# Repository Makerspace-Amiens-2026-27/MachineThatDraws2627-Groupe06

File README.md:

# Dessinator 2000

> [!IMPORTANT]
> **À modifier** : Le nom est arbitraire et voué à etre changé.
> Je l'ai mis temporairement pour des tests (Sacha S).

Une phrase qui explique ce que fait le projet et pour qui.

- **Documentation :** [site du projet](https://makerspace-amiens-2026-27.github.io/MachineThatDraws2627-Groupe06/) (sources dans [`docs/`](docs/))
- **Fichiers du projet :** [`project/`](project/) (CAO, électronique, code)

## Équipe

| Membre | Formation | Compte GitHub |
|---|---|---|
| Sacha SZESTAK | joueur pokemon go  | [@Sacha-SZESTAK](https://github.com/sacha-SZESTAK) |
| Sacha HALEZA | tryharder GD | [@Sacha-HALEZA](https://github.com/sachahaleza-stack) |
| Adrien SERVANT | consommateur aguerri du distributeur | [@Adrien-SERVANT](https://github.com/Adrien-Servant) |
| Samuel MOATTI | Consommateur engagé au distributeur | [@Samuel-MOATTI](https://github.com/SamuelMOATTI) |
| Louis DUBRAY | PNJ  | [@Louis-DUBAY](https://github.com/louis-DB) |

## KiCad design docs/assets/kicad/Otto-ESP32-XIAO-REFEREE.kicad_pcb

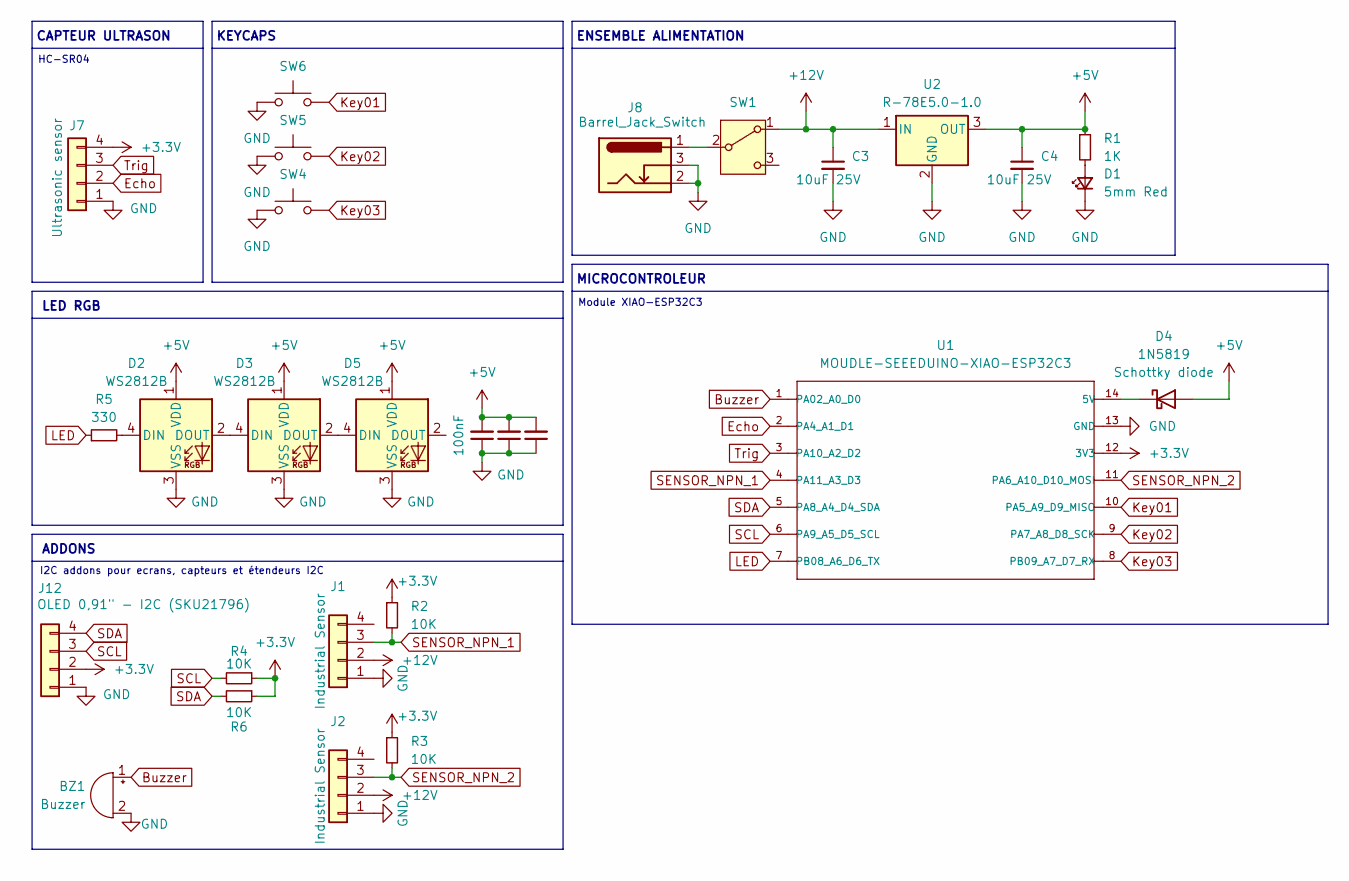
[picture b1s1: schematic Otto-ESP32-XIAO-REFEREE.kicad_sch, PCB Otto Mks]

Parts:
BZ1: Buzzer; Buzzer_12x9.5RM7.6
C3, C4: 10uF 25V; C_Disc_D6.0mm_W2.5mm_P5.00mm
C5, C6, C7: 100nF; C_1206_3216Metric_Pad1.33x1.80mm_HandSolder
D1: 5mm Red; LED_1206_3216Metric_Pad1.42x1.75mm_HandSolder
D2, D3, D5: WS2812B; LED_WS2812B_PLCC4_5.0x5.0mm_P3.2mm
D4: 1N5819; D_A-405_P7.62mm_Horizontal
J1, J2: Industrial Sensor; Molex_KK-254_AE-6410-04A_1x04_P2.54mm_Vertical
J7: Ultrasonic sensor; PinSocket_1x04_P2.54mm_Vertical
J8: Barrel_Jack_Switch; BarrelJack_Horizontal
J12: OLED 0,91" - I2C (SKU21796); PinSocket_1x04_P2.54mm_Vertical
R1: 1K; R_1206_3216Metric_Pad1.30x1.75mm_HandSolder
R2, R3, R4, R6: 10K; R_1206_3216Metric_Pad1.30x1.75mm_HandSolder
R5: 330; R_1206_3216Metric_Pad1.30x1.75mm_HandSolder
SW1: SW_SPDT; SW_100SP1T1B4M2QE
SW4, SW5, SW6: CherryMX; SW_Cherry_MX_1.00u_PCB
U1: MOUDLE-SEEEDUINO-XIAO-ESP32C3; XIAO-ESP32C3-DIP
U2: R-78E5.0-1.0; Converter_DCDC_RECOM_R-78E-0.5_THT

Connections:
+3.3V: J7.4, J12.2, R2.1, R3.1, R4.1, R6.1, U1.12 (3V3)
+5V: C4.1, C5.2, C6.2, C7.2, D2.1 (VDD), D3.1 (VDD), D4.2 (A), D5.1 (VDD), R1.1, U2.3 (OUT)
+12V: C3.1, J1.2, J2.2, SW1.1 (A), U2.1 (IN)
Buzzer: BZ1.1 (+), U1.1 (PA02_A0_D0)
Echo: J7.2, U1.2 (PA4_A1_D1)
GND: BZ1.2 (-), C3.2, C4.2, C5.1, C6.1, C7.1, D1.1 (K), D2.3 (VSS), D3.3 (VSS), D5.3 (VSS), J1.1, J2.1, J7.1, J8.2, J8.3, J12.1, SW4.1, SW5.1, SW6.1, U1.13 (GND), U2.2 (GND)
Key01: SW6.2, U1.10 (PA5_A9_D9_MISO)
Key02: SW5.2, U1.9 (PA7_A8_D8_SCK)
Key03: SW4.2, U1.8 (PB09_A7_D7_RX)
LED: R5.1, U1.7 (PB08_A6_D6_TX)
unnamed: D1.2 (A), R1.2
unnamed: D2.4 (DIN), R5.2
unnamed: D2.2 (DOUT), D3.4 (DIN)
unnamed: D3.2 (DOUT), D5.4 (DIN)
unnamed: D4.1 (K), U1.14 (5V)
unnamed: J8.1, SW1.2 (B)
SCL: J12.3, R4.2, U1.6 (PA9_A5_D5_SCL)
SDA: J12.4, R6.2, U1.5 (PA8_A4_D4_SDA)
SENSOR_NPN_1: J1.3, R2.2, U1.4 (PA11_A3_D3)
SENSOR_NPN_2: J2.3, R3.2, U1.11 (PA6_A10_D10_MOSI)
Trig: J7.3, U1.3 (PA10_A2_D2)

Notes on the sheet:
HC-SR04
CAPTEUR ULTRASON
LED RGB
ADDONS
ENSEMBLE ALIMENTATION
KEYCAPS
Module XIAO-ESP32C3
I2C addons pour ecrans, capteurs et étendeurs I2C
MICROCONTROLEUR

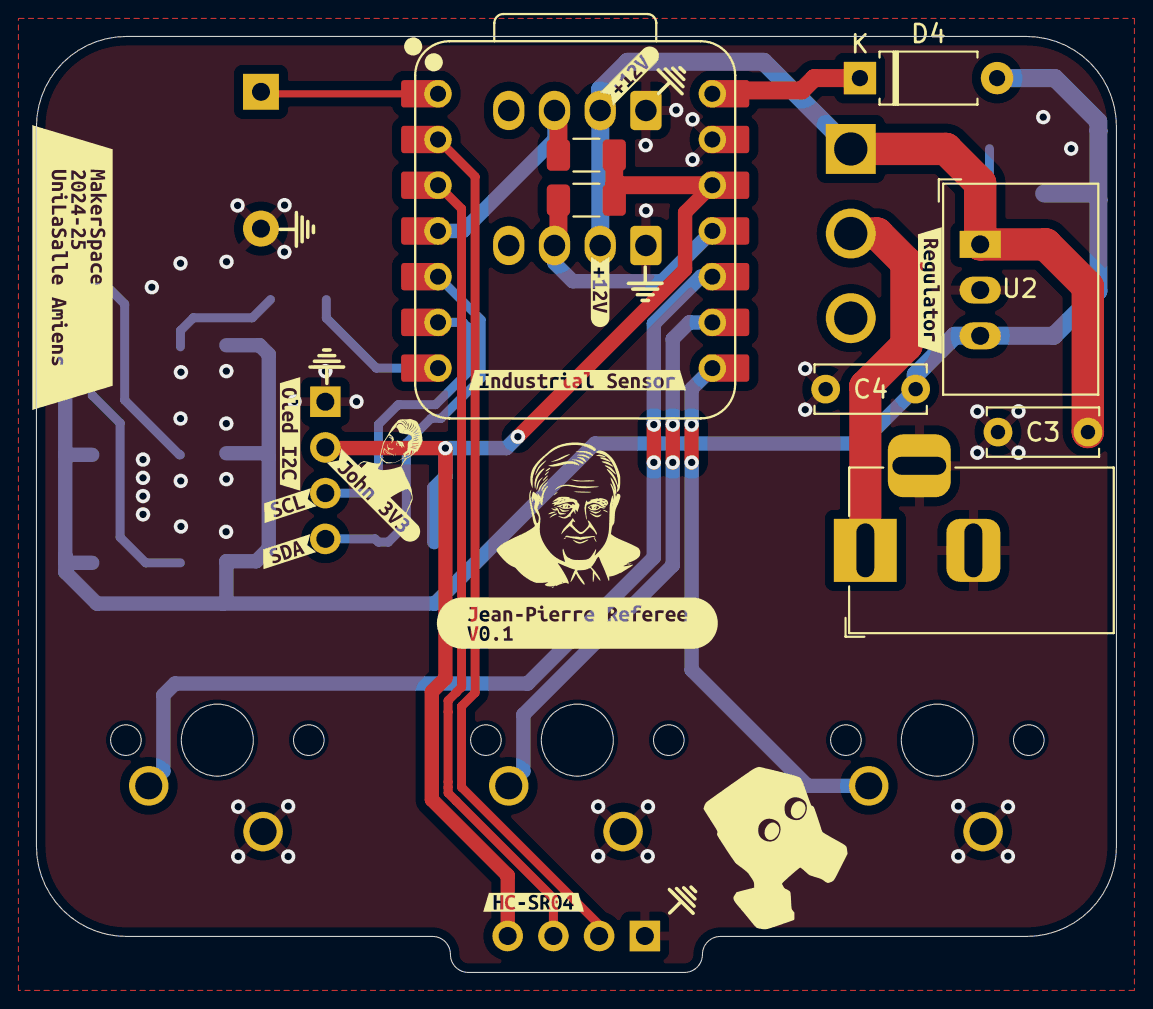
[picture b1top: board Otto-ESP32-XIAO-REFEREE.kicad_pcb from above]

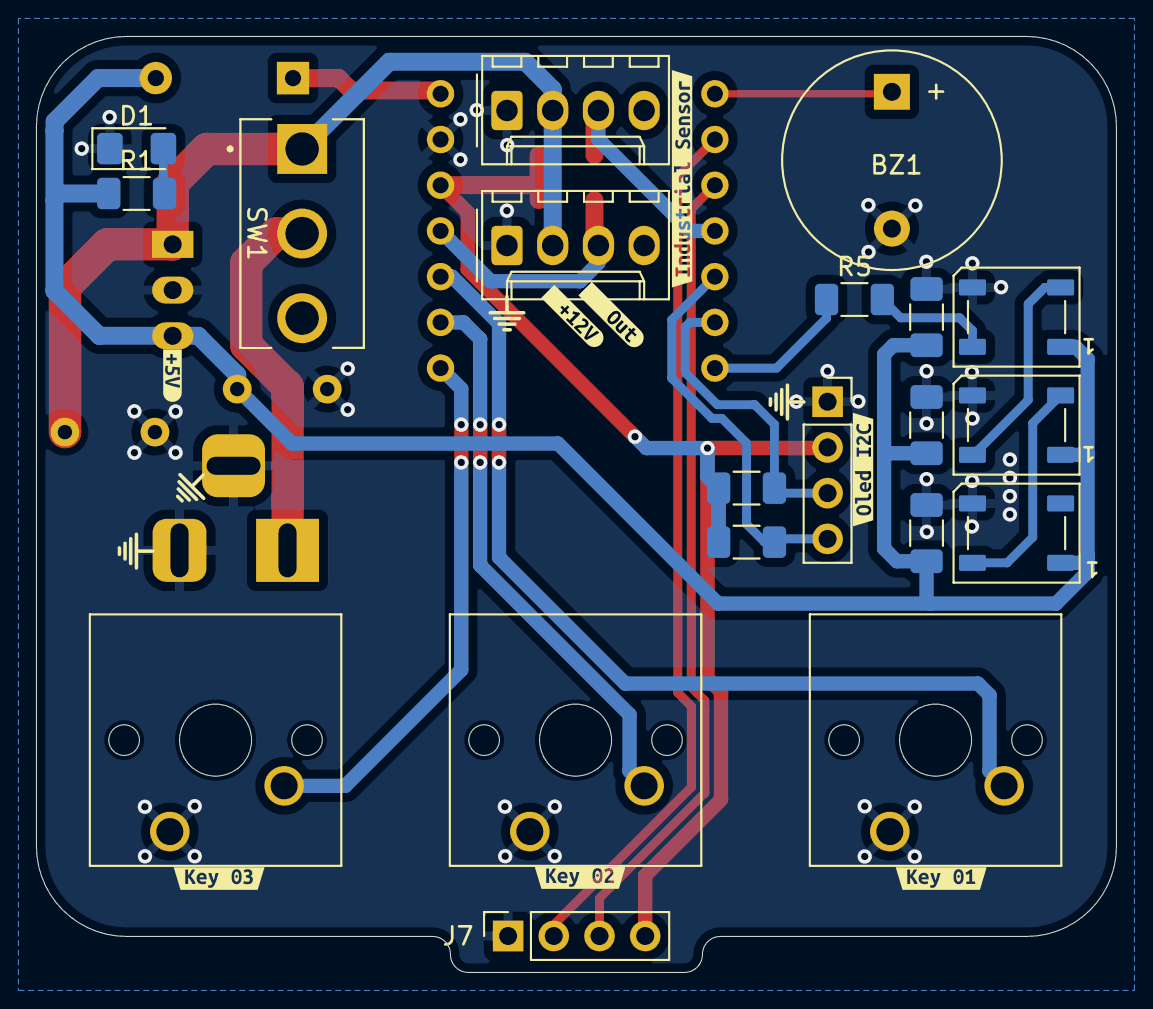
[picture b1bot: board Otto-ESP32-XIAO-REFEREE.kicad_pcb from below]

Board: 2 copper layers, 60.0 x 52.0 mm, 47 parts (28 on the bottom side), 21 nets.

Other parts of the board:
kibuzzard-66E45BAB: G***; kibuzzard-66E45BAB
kibuzzard-66E46157: G***; kibuzzard-66E46157
kibuzzard-67E17B13: G***; kibuzzard-67E17B13
kibuzzard-67E17C5A, kibuzzard-67E17C5A#2: G***; kibuzzard-67E17C5A
kibuzzard-67E17C70: G***; kibuzzard-67E17C70
kibuzzard-67E17CA6: G***; kibuzzard-67E17CA6
kibuzzard-67E17CB8, kibuzzard-67E17CB8#2: G***; kibuzzard-67E17CB8
kibuzzard-67E17911: G***; kibuzzard-67E17911
kibuzzard-67E17954: G***; kibuzzard-67E17954
kibuzzard-67EAB5AA: G***; kibuzzard-67EAB5AA
kibuzzard-67EAB5C2: G***; kibuzzard-67EAB5C2
kibuzzard-67EAB5C7: G***; kibuzzard-67EAB5C7
kibuzzard-67EAB37B: G***; kibuzzard-67EAB37B
kibuzzard-67EAB421: G***; kibuzzard-67EAB421
kibuzzard-6707C6B3: G***; kibuzzard-6707C6B3
kibuzzard-6765451E: G***; kibuzzard-6765451E
kibuzzard-67654523: G***; kibuzzard-67654523
